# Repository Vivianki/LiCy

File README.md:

## Synopsis

Final project for Computer Engineering at University Of São Paulo.
PHY I implementation of IEEE 802.15.7 Li-Fi standard. Mostly done in VHDL for Cyclone IV FPGA.

## Motivation

Li-Fi applications are varied as a result of its key features, such as 
* directional lighting, 
* energy efficiency, 
* intrinsic security, 
* high data rate capability, 
* signal blocking by walls and 
* integrated networking capability.

Therefore it has a various applications in: 

* Security,
* Dense urban environments, 
* Electromagnetic interference sensitive environments,
* Safety environments,
* Intelligent transportation systems,
* Indoor navigation,
* Sensitive data

## Tests

Testing is done using VHDL Test Bench files.

## License

This project is under Apache 2.0 licence.

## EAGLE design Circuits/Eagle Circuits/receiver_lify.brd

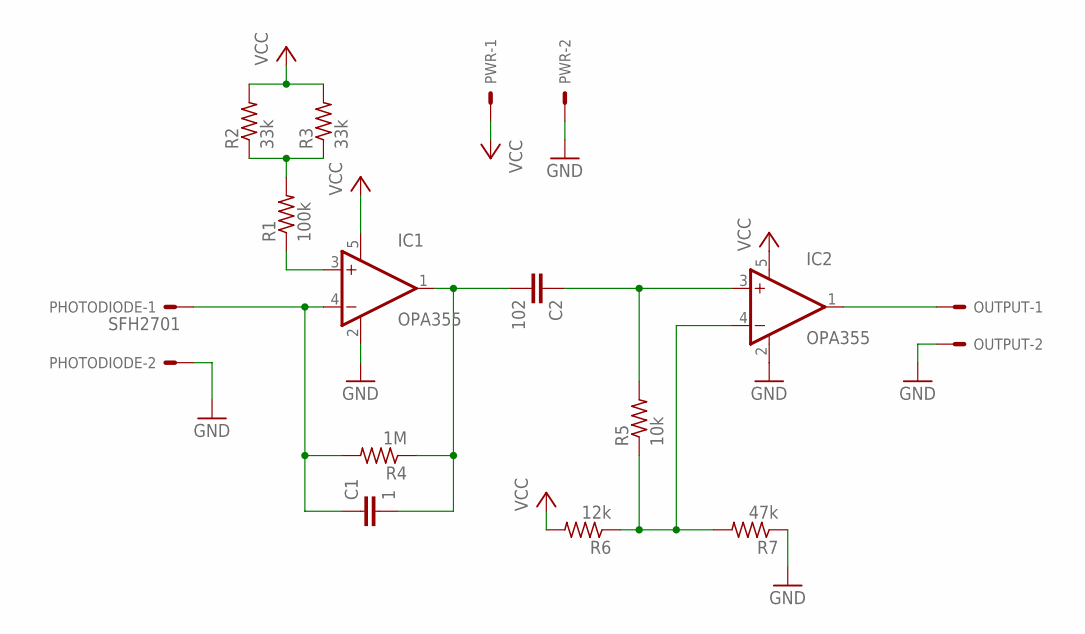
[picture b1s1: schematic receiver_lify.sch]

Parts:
C1: 1; C050-025X075
C2: 102; C050-025X075
IC1, IC2: OPA355; SOT23-5
OUTPUT: 22-23-2021
PHOTODIODE: SFH2701; 22-23-2021
PWR: 22-23-2021
R1: 100k; 0204/7
R2, R3: 33k; 0204/7
R4: 1M; 0204/7
R5: 10k; 0204/7
R6: 12k; 0204/7
R7: 47k; 0204/7

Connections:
GND: IC1.2 (V-), IC2.2 (V-), OUTPUT.2, PHOTODIODE.2, PWR.2, R7.1
unnamed: C1.1, IC1.4 (-IN), PHOTODIODE.1, R4.2
unnamed: IC1.3 (+IN), R1.1
unnamed: R1.2, R2.1, R3.1
unnamed: C1.2, C2.2, IC1.1 (OUT), R4.1
unnamed: IC2.4 (-IN), R5.1, R6.1, R7.2
unnamed: C2.1, IC2.3 (+IN), R5.2
unnamed: IC2.1 (OUT), OUTPUT.1
VCC: IC1.5 (V+), IC2.5 (V+), PWR.1, R2.2, R3.2, R6.2

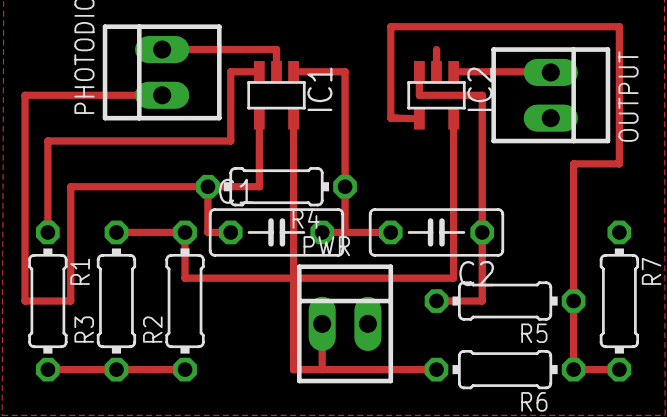
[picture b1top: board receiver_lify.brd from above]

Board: 2 copper layers, 14 parts (0 on the bottom side), 9 nets.

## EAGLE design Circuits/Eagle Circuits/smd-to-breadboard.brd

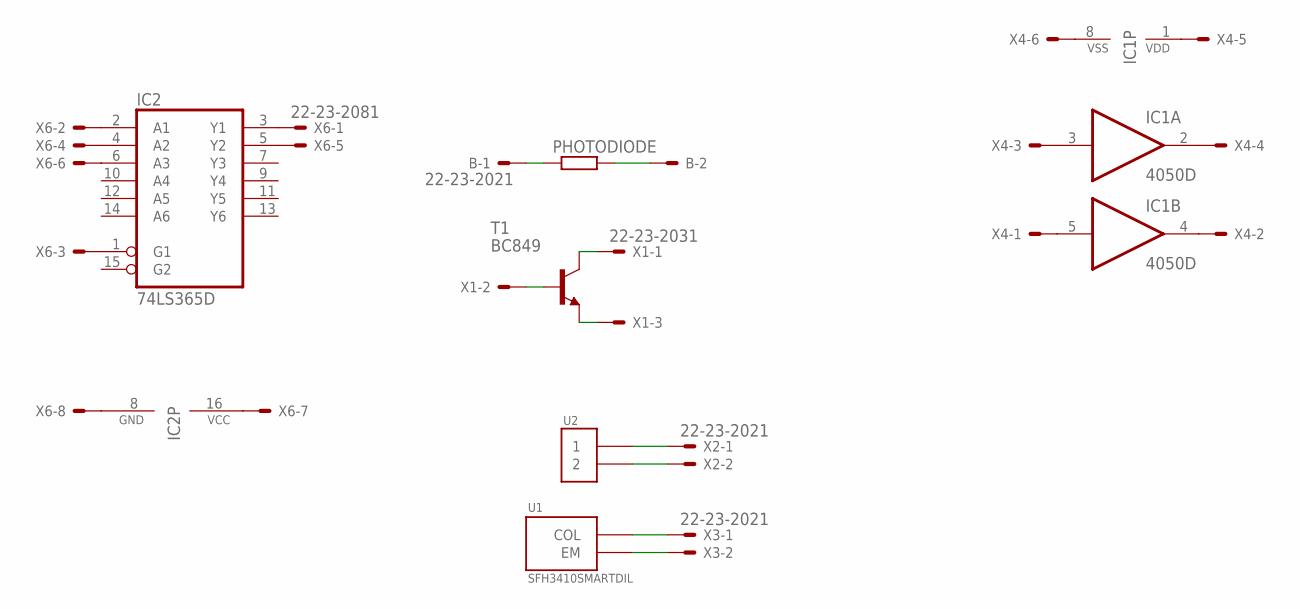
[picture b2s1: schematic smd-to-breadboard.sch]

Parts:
B: 22-23-2021
IC1: 4050D; SO16
IC2: 74LS365D; SO16
PHOTODIODE: RR1206; R1206
T1: BC849; SOT23
U1: SFH3410SMARTDIL; SFH3410
U2: LUW-W5AMGULLWING; LUW-W5AM
X1: 22-23-2031
X2, X3: 22-23-2021
X4: 22-23-2061
X6: 22-23-2081

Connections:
unnamed: B.1, PHOTODIODE.1
unnamed: B.2, PHOTODIODE.2
unnamed: T1.3 (C), X1.1
unnamed: T1.1 (B), X1.2
unnamed: T1.2 (E), X1.3
unnamed: U2.1, X2.1
unnamed: U2.2, X2.2
unnamed: U1.1 (COL), X3.1
unnamed: U1.2 (EM), X3.2
unnamed: IC1.5 (I), X4.1
unnamed: IC1.3 (I), X4.3
unnamed: IC1.2 (O), X4.4
unnamed: IC1.4 (O), X4.2
unnamed: IC2.3 (Y1), X6.1
unnamed: IC2.2 (A1), X6.2
unnamed: IC2.1 (G1), X6.3
unnamed: IC2.16 (VCC), X6.7
unnamed: IC2.8 (GND), X6.8
unnamed: IC1.8 (VSS), X4.6
unnamed: IC1.1 (VDD), X4.5
unnamed: IC2.4 (A2), X6.4
unnamed: IC2.5 (Y2), X6.5
unnamed: IC2.6 (A3), X6.6

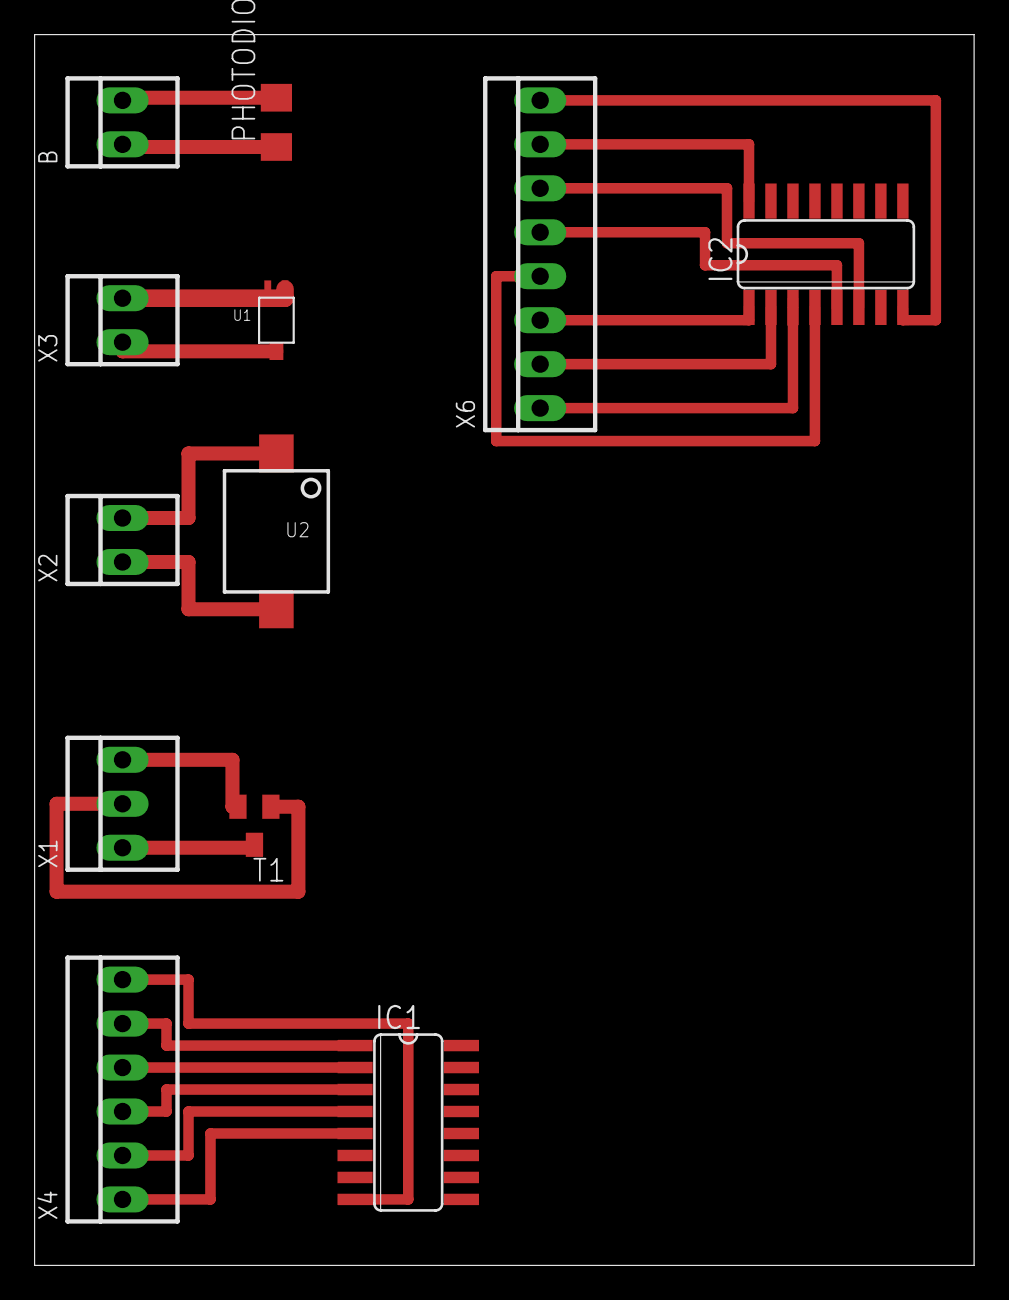
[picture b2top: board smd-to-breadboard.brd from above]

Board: 2 copper layers, 54.3 x 71.1 mm, 12 parts (0 on the bottom side), 23 nets.

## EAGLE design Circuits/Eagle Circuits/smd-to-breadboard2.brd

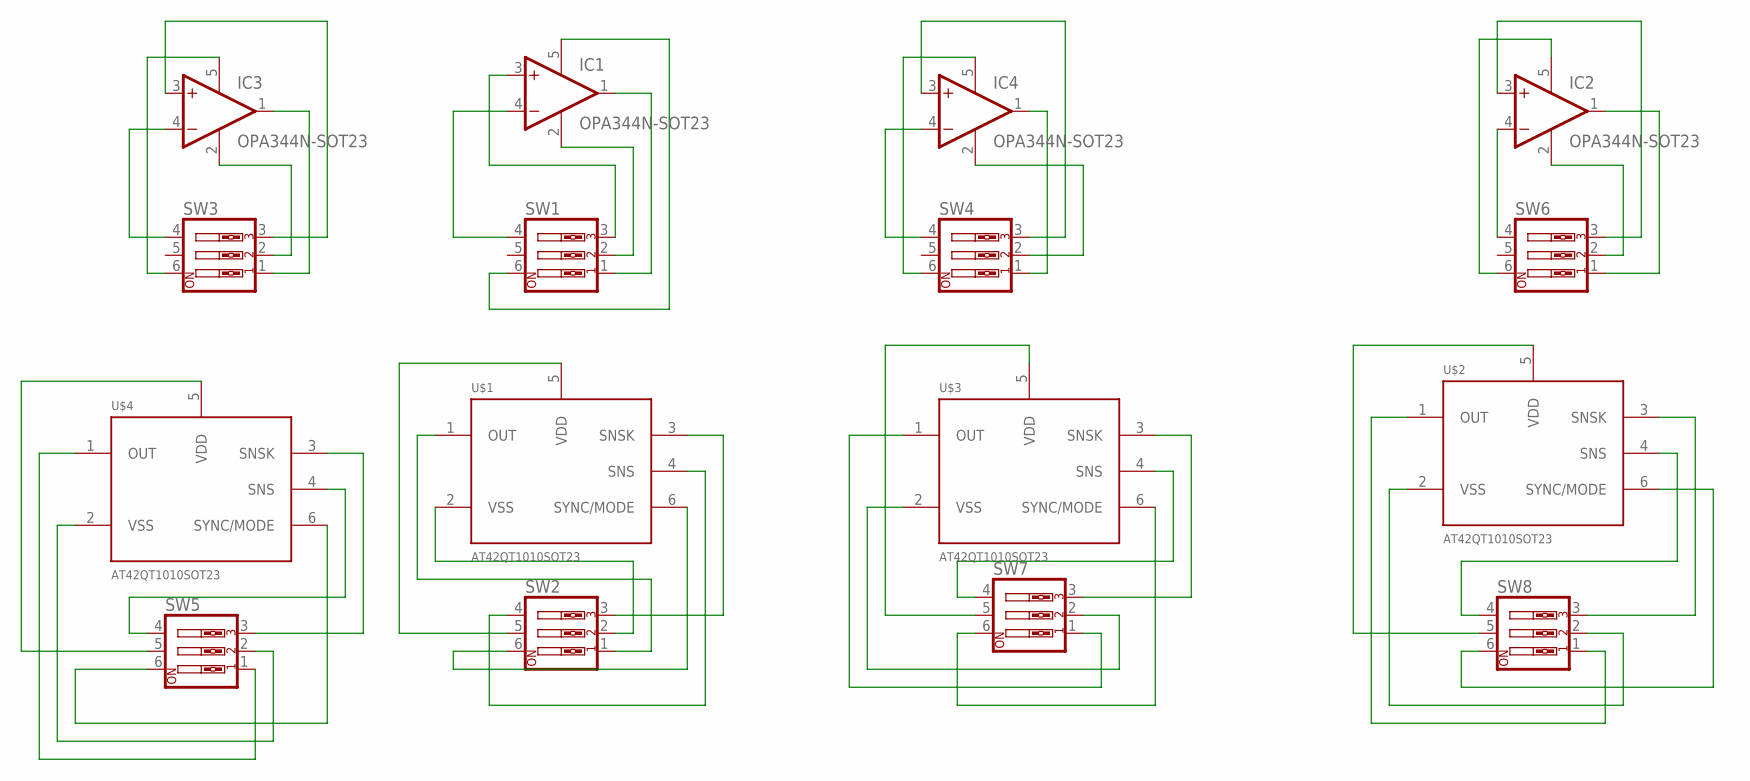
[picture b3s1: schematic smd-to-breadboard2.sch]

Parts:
IC1, IC2, IC3, IC4: OPA344N-SOT23; SOT23-5
SW1, SW2, SW3, SW4, SW5, SW6, SW7, SW8: SW_DIP-3; EDG-03
U$1, U$2, U$3, U$4: AT42QT1010SOT23; SOT23-6

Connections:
unnamed: IC3.1 (OUT), SW3.1
unnamed: IC3.2 (V-), SW3.2
unnamed: IC3.3 (+IN), SW3.3
unnamed: IC3.5 (V+), SW3.6
unnamed: IC3.4 (-IN), SW3.4
unnamed: IC4.3 (+IN), SW4.3
unnamed: IC4.5 (V+), SW4.6
unnamed: IC4.4 (-IN), SW4.4
unnamed: IC4.1 (OUT), SW4.1
unnamed: IC1.1 (OUT), SW1.1
unnamed: IC1.2 (V-), SW1.2
unnamed: IC1.5 (V+), SW1.6
unnamed: IC1.3 (+IN), SW1.3
unnamed: IC1.4 (-IN), SW1.4
unnamed: SW2.1, U$1.1 (OUT)
unnamed: SW2.6, U$1.6 (SYNC/MODE)
unnamed: SW2.2, U$1.2 (VSS)
unnamed: SW2.4, U$1.4 (SNS)
unnamed: SW2.5, U$1.5 (VDD)
unnamed: SW2.3, U$1.3 (SNSK)
unnamed: IC4.2 (V-), SW4.2
unnamed: IC2.4 (-IN), SW6.4
unnamed: IC2.5 (V+), SW6.6
unnamed: IC2.3 (+IN), SW6.3
unnamed: IC2.1 (OUT), SW6.1
unnamed: IC2.2 (V-), SW6.2
unnamed: SW5.1, U$4.1 (OUT)
unnamed: SW5.2, U$4.2 (VSS)
unnamed: SW5.5, U$4.5 (VDD)
unnamed: SW5.6, U$4.6 (SYNC/MODE)
unnamed: SW5.4, U$4.4 (SNS)
unnamed: SW5.3, U$4.3 (SNSK)
unnamed: SW7.1, U$3.1 (OUT)
unnamed: SW7.2, U$3.2 (VSS)
unnamed: SW7.6, U$3.6 (SYNC/MODE)
unnamed: SW7.5, U$3.5 (VDD)
unnamed: SW7.4, U$3.4 (SNS)
unnamed: SW7.3, U$3.3 (SNSK)
unnamed: SW8.1, U$2.1 (OUT)
unnamed: SW8.2, U$2.2 (VSS)
unnamed: SW8.3, U$2.3 (SNSK)
unnamed: SW8.4, U$2.4 (SNS)
unnamed: SW8.5, U$2.5 (VDD)
unnamed: SW8.6, U$2.6 (SYNC/MODE)

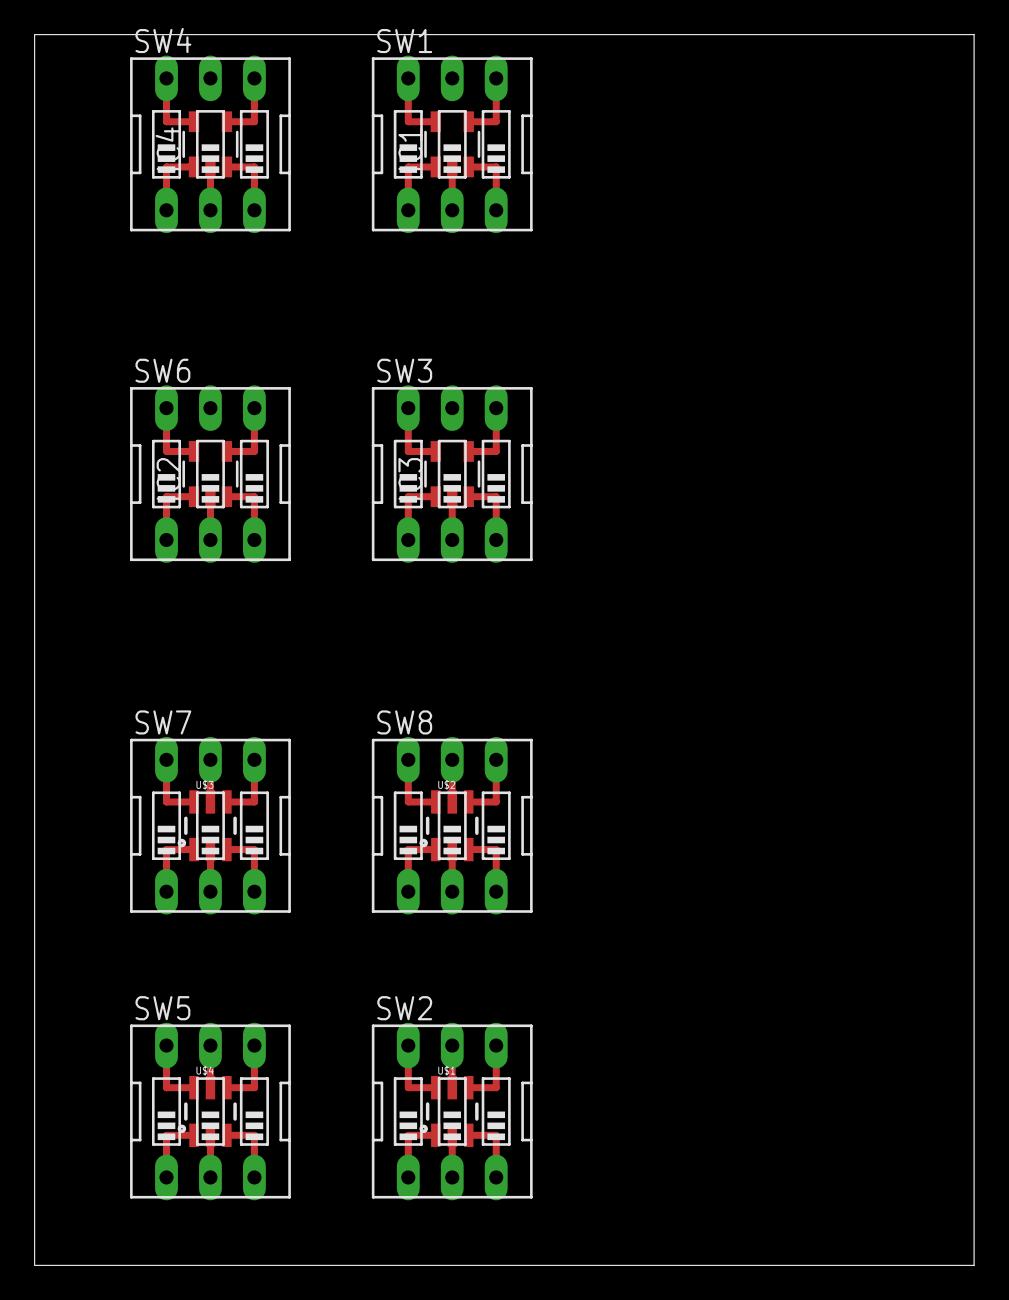
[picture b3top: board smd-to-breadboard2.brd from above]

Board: 2 copper layers, 54.3 x 71.1 mm, 16 parts (0 on the bottom side), 44 nets.

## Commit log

2016-03-27 Initial commit
    First commit to repository!
2016-03-27 Included MSProject mockup file
    Needs WBS
2016-03-28 Documents folder + WBS + Gantt
    Files moved and updated MS Project file with actual WBS data
2016-03-30 Drawing, Gantt update & Requirements Tree
    LiCy concept drawing for future reference, gantt references update and
    requirements tree added.
2016-03-31 Product Description
    Inclusion of first version
2016-04-19 Removed documents and added report
    Also added how-to
2016-04-19 Updated report and added gitignore
    Added start of introduction and renamed file
2016-04-19 Gitignore update
2016-04-22 Updated some references
    Addded some of the introduction, still managing citation
2016-04-22 % in URL
    fixed, as well as a issue when dealing with urls too long
2016-04-22 Wrong URL
    Fixed double slash issue when compiling!
2016-04-22 Modular redesign and unrelated content
    Allows better separation of content. Removed unrelated content from main
    document, such as AbnteX examples.
2016-04-23 Added abstract file and removed some references
    Also removed some additional files, such as "Erratas"
2016-04-26 Added mockup ampop circuit
2016-04-26 FPGA
2016-04-27 FPGA
    Complementando justificativa para escolha da FPGA
2016-04-28 LED
    Details and testing
2016-04-29 Motivação
    seção de motivação com referência ao projeto anterior
2016-04-29 Planejamento
    Inclusão da seção de planejamento e subitens
2016-05-01 OpAmp + Circuit
2016-05-15 Decoder VHDL
    Início da implementação do decoder, com calculo da síndrome
2016-05-16 RS Encoder logic and testbench
2016-05-18 Adicoes no relatorio
2016-05-20 Fixed wrong merge
2016-06-13 [report] Added gantt, updated requirements (Felippe), added methods
2016-06-13 [report] added details on tx
2016-06-15 [report] requirements tree updated
2016-09-08 Added Sync
    Lots of work this time, simulation also included in the VHDL Simulations
    folder
2016-09-09 Atualizações Felippe
    Manchester Decoder, RS Decoder (incompleto), RS enc/dec em JavaScript (
    15, 7 em progresso)
2016-09-14 Decodificador JS
    Quase completo, mas só corrige 1 símbolo errado, quando deveria
    corrigir 4.
    Faltam comentários.
2016-09-19 Protótipo Reed Solomon
    Em funcionamento, pronto para geração de entradas e para conferir
    resultados com VHDL.
2016-09-22 Added Interleaver code
    Still trying to figure out how to include ram component into
    interleaver.
    Javascript code is included, where the interleaving process happens at a
    higher level to help understanding.
2016-09-22 WORKING SYNC
    credits to @Vivianki
2016-09-24 Updating readme
2016-09-24 Fixed spacing
2016-09-24 Syndrome Testbench
2016-09-24 Added gitignore for interleaver
2016-09-24 Gitignored?
2016-09-24 Revert "Gitignored?"
    This reverts commit 21132df916af13093f550c58a404dcbdfbc67093.
2016-09-24 Revert "Revert "Gitignored?""
    This reverts commit 3a3e0cbc048d2befd00cba55cc0494af94c73ab0.
2016-09-24 I promise I'm trying
2016-09-24 Testbench Berlekamp
    incompleto - by @felippedr
2016-09-25 Added Arduino Square Wave Generator
    And sync proof as a bonus
2016-09-25 Convolutional Encoder & Viterbi
    Integration and FPGA Testing done!
    @Vivianki
2016-09-25 Adding deinterleaver
2016-09-25 Deinterleaver workaround
2016-09-25 Simulation working
    Small fixes to interleaver and deinterleaver
2016-09-25 RS Encoding latches fix
2016-09-28 Interleaver Rev2
    Not working, trying things out
2016-09-29 Interleaver Rev2 Fix
    Still not working, needs more work. work by @Vivianki
2016-10-01 Berlekamp Testbench
    @felippedr @gabrieltnishimura
2016-10-01 Berlekamp Massey - Testbench
    Funcionando, mas precisa de mais alguns ajustes para integração.
    Verificar questão da borda de descida / subida.
    by @felippedr e @gabrieltnishimura
2016-10-01 Chien Testbench
    Funcionando, mas falta integração.
2016-10-01 Integração Chien + Forney
    Com testbench. Falta detecção de mais de 4 erros.
2016-10-01 Tentativa de integração Berlekamp + ChienForney
    mal sucedida
2016-10-01 RSDec - Berlekamp Counter
    Working simulation
2016-10-01 Integração Berlekamp + Chien + Forney
    by @felippedr e @gabrieltnishimura
2016-10-11 Added some comentaries on circuitry
2016-10-12 [report] Added lots of todos
2016-10-13 Interleaver Modifications
    Working with no testbench
2016-10-13 Added gitignore
2016-10-13 Gitignore2
2016-10-13 Added encoder integration
    RS Encoder + Interleaver on its way
2016-10-13 Integração parcial Reed SOlomon Decoder
    Falta a máquina de estados da síndrome funcionar
2016-10-13 Reed Solomon Integrado
    Faltam buffers da mensagem e flag de erro
2016-10-13 Interleaver with payload done
    Needs testing
2016-10-13 Report and Convolutional Puncture
    By @gabrieltnishimura and @Vivianki
2016-10-13 Interleaver integrated with RS Encoder
    @Vivianki
2016-10-13 Adding convolutional encoder to Encoder
    Not fully integrated yet.
2016-10-20 Signal Tap + Interleaver Integrated
2016-11-02 Reed Solomon
    com cálculo de erro e quase pronto para integração no pipeline
2016-11-03 Reed Solomon Decoder
    Completo, pronto para integração
2016-11-03 Read me de reed solomon decoder
    Reed Solomon Decoder/Read Me
2016-11-03 Encoder Integration + Decoder start
2016-11-06 UART
    FPGA -> Computer working
2016-11-07 Integração
2016-11-08 Working Interleaver + Viterbi integration
2016-11-09 New UART with debounce
    It works for a character RX and TX, need to extend to register fifo
    logic
2016-11-12 Working RSEncoder-Deinterleaver integration
    aLmost there!!!!111
2016-11-12 Integration RSEncoder-RSDecoder
    UART missing
2016-11-12 Refactored Project and Added Circuits/Simulations
    Maybe some linking problems with RSEncoder
2016-11-14 Reed Solomon
    Faltam explicação teórica de berlekamp, imagens e fórmulas
2016-11-15 Added circuit report
    still needs lot of work
2016-11-16 Teoria de Reed Solomon
    Quase completa, faltam imagens, diagramas, algumas fórmulas. Possível
    melhorar a explicação para Berlekamp.
2016-11-17 Report Updates
    new assets, new graphs lib, etc
2016-11-17 Metologia Update
    Manchester, VHDL
2016-11-17 Reorganização relatório
    otmização da organização de alguns tópicos
2016-11-17 Funcionou?
    Pls no break anymore
2016-11-18 Metologia
    Reed Solomon completo com diagramas. Necessário melhorar algumas
    justificativas
2016-11-18 Finalização da metodologia de hardware
2016-11-18 Posters
    modelos
2016-11-19 Modificações na metodologia inicial
2016-11-23 Updates on report
2016-11-24 Pre-commit
2016-11-24 TX and RX working on the FPGA
    Connecting cable between exposed pins! Yey
2016-11-24 Execution partial
2016-11-24 Needs more execution
2016-11-25 Analog Finished
    Need to fix citations
2016-11-26 end of metodologia
2016-11-27 Execução Reed Solomon
2016-11-27 Methods revision
    added some acronyms, added standard to naming labels, etc
2016-11-27 Diagrams reloaded
2016-11-27 Correções de meto e intro
    Adequação a mudança de escopo do projeto
2016-11-27 Dots dots dots and some other stuff
2016-11-27 Conclusão
    Revisem pls
2016-11-27 Resources and text that needs revision
    Convolutional, Interleaver, Manchester Decoder, UART and Viterbi
2016-11-27 Found a mistake
2016-11-29 Modificações
    Trim, textos, anexos
2016-11-29 Sync execution added
2016-11-29 Intro + abstract
    faltam palavras chave
2016-11-29 Added RTLs, wrapped up interleaver, minor modifications.
    Still need to do convolutional and viterbi
2016-11-29 Italic and somewhat new structure
2016-11-29 Trimmed all simulations, fixed all wrong doings in the world, wrote viterbi and conv execution
2016-11-29 Revisão Caro
2016-11-30 Agradecimentos
    #thorzz
2016-11-30 Modificações no arquivo de configurações
2016-11-30 Images are all fixed now!
2016-11-30 Alterações finais Felippe
    faltam alguns itens da bibliografia D:
2016-11-30 Últimas modificações, resultados removidos
2016-11-30 Bruno rev
2016-11-30 Bruno rev 2
2016-11-30 Appendix
2016-11-30 fix do nome + removida ficha catalografica
2016-11-30 Referencias do RS
    por favor revisar e verificar se funciona antes de gerar
2016-11-30 more
2016-12-13 Cyclone 5 Implementation
    integrations on the way
2016-12-15 Cyclone 5 Tweaking, ITS WORKING
2016-12-15 Added Java Client to have fun!
    Hopefully last productive commit!
2016-12-26 Começo da revisão!
2016-12-27 Revisão Bibliográfica começada
2017-01-09 Revisão Bibliográfica quase terminada
    Preciso que alguém verifique como ficaram os nossos acronyms
2017-01-10 intro e conclusão incompletas
    falta o fugging problema de engenharia
2017-01-11 Introdução e conclusão
    completas talvez... validemos
2017-01-11 Testes +/-, tabela comparativa para revisao bibliografica e ajustes gerais
    PDF mais atual adicionado ao git

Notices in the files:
parts and their libraries:
SparkFun-DigitalIC: Licensing: Creative Commons ShareAlike 4.0 International - https://creativecommons.org/licenses/by-sa/4.0
